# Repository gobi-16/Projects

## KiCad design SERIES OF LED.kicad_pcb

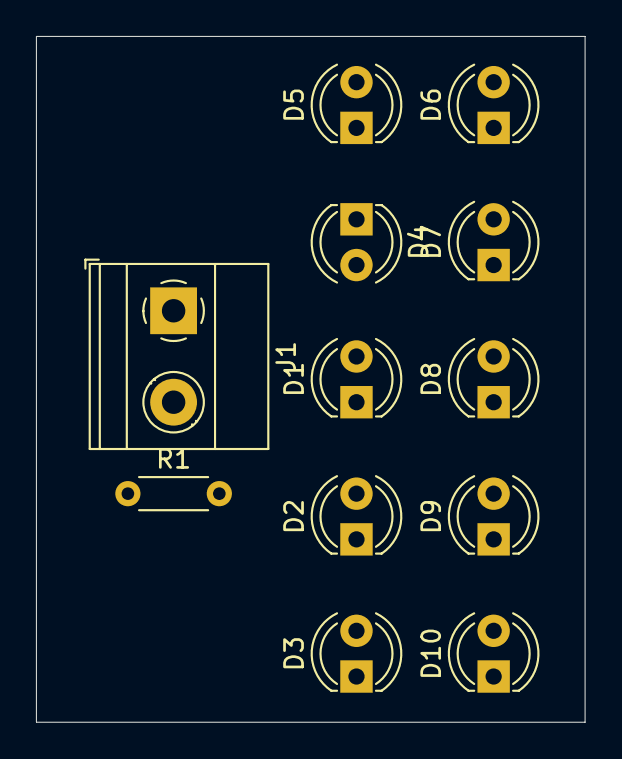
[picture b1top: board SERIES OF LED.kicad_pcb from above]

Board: 2 copper layers, 30.5 x 38.1 mm, 12 parts (0 on the bottom side), 11 nets, no tracks yet.

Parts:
D1, D2, D3, D4, D5, D6, D7, D8, D9, D10: LED; LED_D4.0mm
J1: Screw_Terminal_01x02; TerminalBlock_Phoenix_MKDS-1,5-2-5.08_1x02_P5.08mm_Horizont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
R1: 56; R_Axial_DIN0204_L3.6mm_D1.6mm_P5.08mm_Horizontal

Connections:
unnamed: D1.2 (A), D4.1 (K)
unnamed: D1.1 (K), D2.2 (A)
unnamed: D2.1 (K), D3.2 (A)
unnamed: D4.2 (A), D5.1 (K)
unnamed: D5.2 (A), D6.2 (A), J1.1
unnamed: D6.1 (K), D7.2 (A)
unnamed: D7.1 (K), D8.2 (A)
unnamed: D8.1 (K), D9.2 (A)
unnamed: D9.1 (K), D10.2 (A)
unnamed: D3.1 (K), D10.1 (K), R1.2
unnamed: J1.2, R1.1

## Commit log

2024-08-31 Pcb design
2024-08-31 Create PCB Design
2024-08-31 Create vc
2024-08-31 Create as
